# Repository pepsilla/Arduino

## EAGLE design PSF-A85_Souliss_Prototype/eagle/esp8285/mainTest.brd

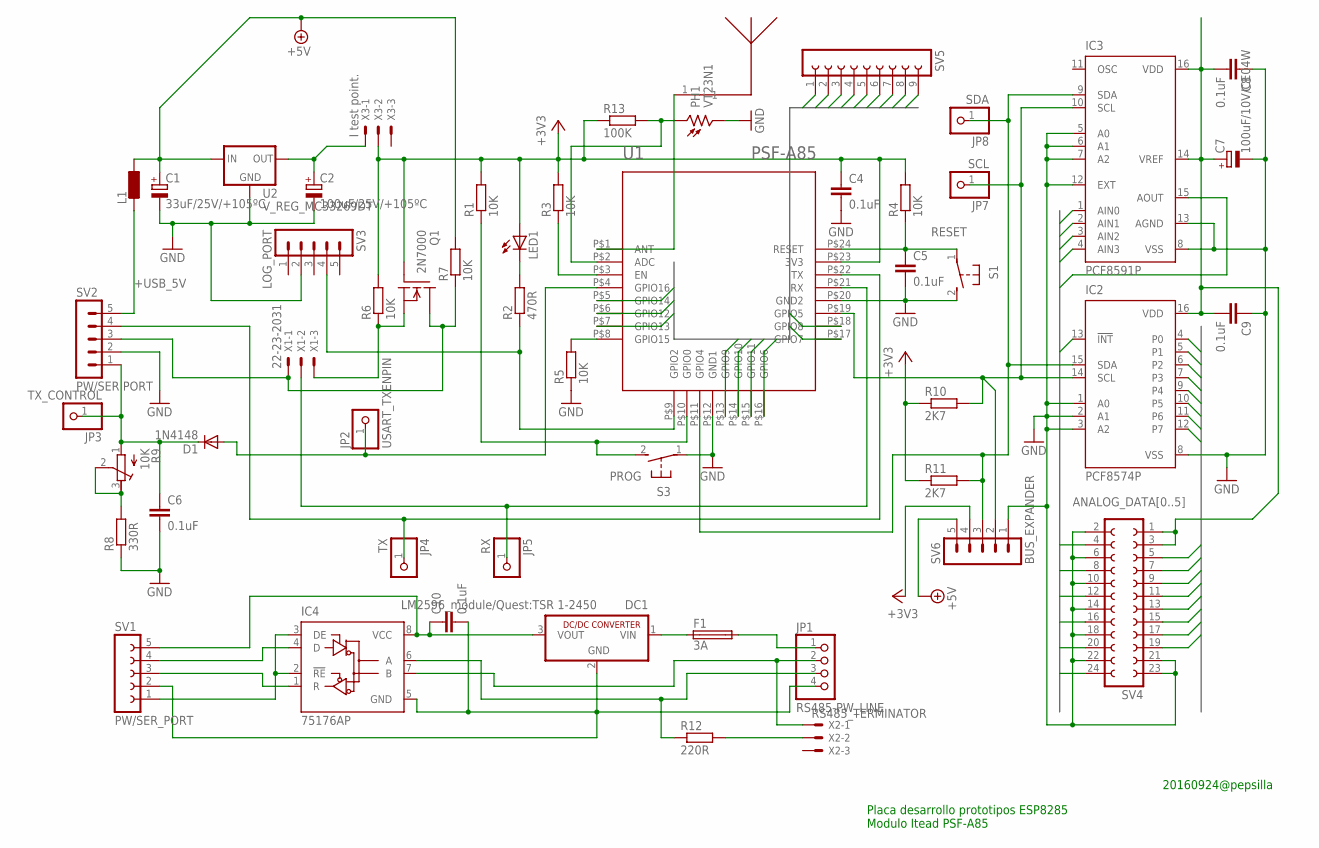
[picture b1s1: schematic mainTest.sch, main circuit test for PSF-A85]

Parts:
C1: 33uF/25V/+105ºC; E3,5-10
C2: 100uF/25V/+105ºC; E3,5-10
C4, C5, C6, C8, C9, C10: 0.1uF; C025-030X050
C7: 100uF/10V/CE04W; E3,5-10
D1: 1N4148; SOD123
DC1: LM2596_module/Quest:TSR 1-2450; SIP3
F1: 3A; TR5
IC2: PCF8574P; DIL16
IC3: PCF8591P; DIL16
IC4: 75176AP; DIL08
JP1: RS485-PW_LINE; 1X04
JP2: USART_TXENPIN; 1X01
JP3: TX_CONTROL; 1X01
JP4: TX; 1X01
JP5: RX; 1X01
JP7: SCL; 1X01
JP8: SDA; 1X01
L1: L0207/10; 0207/10
LED1: LED_E; LED_1206
PH1: VT23N1; TO46-VT200
Q1: 2N7000; TO92
R1, R3, R4, R5, R6, R7: 10K; R0805
R2: 470R; R0805
R8: 330R; R0805
R9: 10K; RTRIM3296X
R10, R11: 2K7; R0805
R12: 220R; R0805
R13: 100K; R0805
S1, S3: 31-XX; B3F-31XX
SV1: PW/SER_PORT; FE05-1
SV2: PW/SER PORT; MA05-1
SV3: LOG_PORT; MA05-1
SV4: FE12-2
SV5: FE09-1; FE09
SV6: BUS_EXPANDER; MA05-1
U1: PSF-A85
U2: V_REG_MC33269DT; DPAK
U$1: PCB-2G4-ANTENNA
X1: 22-23-2031
X2: RS485_TERMINATOR; 22-23-2031
X3: I test point.; 22-23-2031

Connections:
+3V3: C4.1, LED1.A, Q1.1 (G), R1.2, R3.2, R4.2, R6.2, R10.1, R11.1, R13.1, SV6.4, U1.P$23 (3V3), X3.2
+5V: C1.+, L1.1, R7.2, SV6.5, U2.3 (IN)
+USB_5V: L1.2, SV2.5
ANALOG_DATA0: IC3.4 (AIN3), SV4.4
ANALOG_DATA1: IC3.3 (AIN2), SV4.8
ANALOG_DATA2: IC3.2 (AIN1), SV4.12
ANALOG_DATA3: IC3.1 (AIN0), SV4.16
ANALOG_DATA4: IC3.15 (AOUT), SV4.20
ANALOG_DATA5: IC2.13 (!INT), SV4.24
DIGITAL_DATA0: IC2.4 (P0), SV4.5
DIGITAL_DATA1: IC2.5 (P1), SV4.7
DIGITAL_DATA2: IC2.6 (P2), SV4.9
DIGITAL_DATA3: IC2.7 (P3), SV4.11
DIGITAL_DATA4: IC2.9 (P4), SV4.13
DIGITAL_DATA5: IC2.10 (P5), SV4.15
DIGITAL_DATA6: IC2.11 (P6), SV4.17
DIGITAL_DATA7: IC2.12 (P7), SV4.19
GND: C1.-, C2.-, C4.2, C5.2, C6.2, C7.-, C8.1, C9.1, IC2.1 (A0), IC2.2 (A1), IC2.3 (A2), IC2.8 (VSS), IC3.5 (A0), IC3.6 (A1), IC3.7 (A2), IC3.8 (VSS), IC3.12 (EXT), IC3.13 (AGND), PH1.2, R5.1, R8.1, S1.2 (S), S3.1, SV2.2, SV3.2, SV4.2, SV4.6, SV4.10, SV4.14, SV4.18, SV4.21, SV4.22, SV4.23, SV6.1, U1.P$12 (GND1), U1.P$20 (GND2), U2.1 (GND)
unnamed: PH1.1, R13.2, U1.P$2 (ADC)
unnamed: R3.1, U1.P$3 (EN)
unnamed: R2.1, SV3.4, U1.P$9 (GPIO2)
unnamed: R1.1, S3.2 (S), U1.P$10 (GPIO0)
unnamed: R5.2, U1.P$8 (GPIO15)
unnamed: DC1.1 (VIN), F1.1
unnamed: IC2.15 (SDA), IC3.9 (SDA), JP8.1, R11.2, SV6.3, U1.P$11 (GPIO4)
unnamed: C10.1, DC1.3 (VOUT), IC4.8 (VCC), SV1.5
unnamed: C10.2, DC1.2 (GND), IC4.5 (GND), JP1.4, SV1.2
unnamed: IC2.14 (SCL), IC3.10 (SCL), JP7.1, R10.2, SV6.2, U1.P$19 (GPIO5)
unnamed: F1.2, JP1.1
unnamed: R8.2, R9.2 (S), R9.3 (E)
unnamed: Q1.3 (S), R6.1, X1.3
unnamed: LED1.C, R2.2
unnamed: D1.A, JP2.1, U1.P$4 (GPIO16)
unnamed: IC4.7 (B), JP1.2, X2.1
unnamed: IC4.6 (A), JP1.3, R12.1
unnamed: IC4.2 (!RE), IC4.3 (DE), SV1.1
unnamed: IC4.1 (R), SV1.3
unnamed: IC4.4 (D), SV1.4
unnamed: R12.2, X2.2
unnamed: C2.+, U2.4 (OUT), X3.1
unnamed: C6.1, D1.C, JP3.1, R9.1 (A), SV2.1
unnamed: C7.+, C8.2, C9.2, IC2.16 (VDD), IC3.14 (VREF), IC3.16 (VDD), SV4.1, SV4.3
unnamed: U1.P$1 (ANT), U$1.1
PIN_HEADER0: SV5.1, U1.P$5 (GPIO14)
PIN_HEADER1: SV5.2, U1.P$6 (GPIO12)
PIN_HEADER2: SV5.3, U1.P$7 (GPIO13)
PIN_HEADER3: SV5.4, U1.P$13 (GPIO9)
PIN_HEADER4: SV5.5, U1.P$14 (GPIO10)
PIN_HEADER5: SV5.6, U1.P$15 (GPIO11)
PIN_HEADER6: SV5.7, U1.P$16 (GPIO6)
PIN_HEADER7: SV5.8, U1.P$17 (GPIO7)
PIN_HEADER8: SV5.9, U1.P$18 (GPIO8)
PROG: JP5.1, U1.P$21 (RX), X1.2
RESET: C5.1, R4.1, S1.1, U1.P$24 (RESET)
RX: JP4.1, SV2.4, U1.P$22 (TX)
TX: Q1.2 (D), R7.1, SV2.3, X1.1

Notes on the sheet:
Placa desarrollo prototipos ESP8285 Modulo Itead PSF-A85
20160924@pepsilla

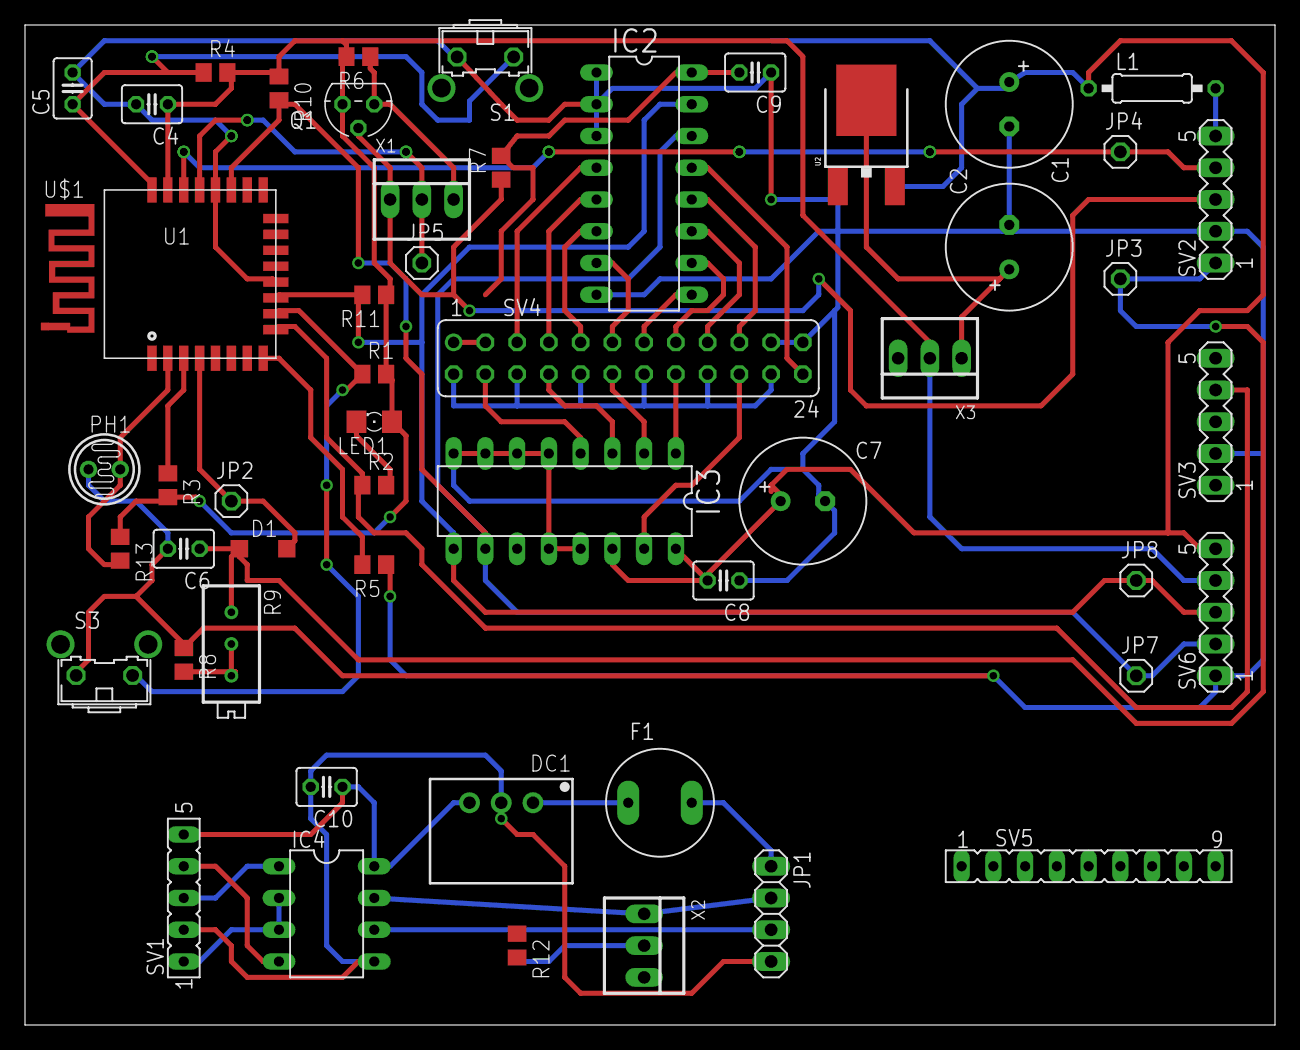
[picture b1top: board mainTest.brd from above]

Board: 2 copper layers, 100.0 x 80.0 mm, 53 parts (0 on the bottom side), 56 nets.

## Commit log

2016-08-24 End of my summer time
    End point of installation tests.
2016-08-24 Schematics
    Added documentation base
2016-09-21 Sample test for Souliss implementation
    Hardware prototype based on itead module PSF-A85
2016-09-27 Eagle project for ESP8285_PROTOTYPE
    Added new free pin connectors, ant pcb and master bus port.
2016-09-27 Optimice work pending
    SCHEMATIC AND PCB
2017-03-08 Arduino Serial Sensoring
    Arduino PlatformIO project and Processing sketch. alpha testing.
2017-09-16 Create README.md
    TODO: Rework libraries for integration PlatformIO and ESP EASY
2018-01-07 InitStatus
    MidiKeyboard_ArduinoDue

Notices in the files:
parts and their libraries:
SparkFun-PowerIC: Licensing: Creative Commons ShareAlike 4.0 International - https://creativecommons.org/licenses/by-sa/4.0
